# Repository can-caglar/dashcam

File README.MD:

# DASHCAM PROJECT

This is the development repo for a low-cost, dash-cam hobby project.

**Features:**

1. Small size (34 x 34 x 34 cm)

2. Saves videos to AVI format (motion JPEG).

3. Powered through a USB mini cable.

4. Can connect to WiFi. The idea is to connect it to your phone hotspot, after which the video will be streamed to a local server that the driver can access on their phone's internet browser. This is to help the driver position the camera by seeing what the camera is seing.

5. Small OLED screen and 3 buttons for the UI. OLED will show the device IP address for the video streaming server, and show nearby WiFi access points.

6. Inexpensive looking (due to very small design). Will not encourage thieves!

7. Has a supercapacitor which keeps power active for ~ 1 second after power is cut, this means videos will never be corrupt.

8. SD card slot which overrides oldest videos, so the device will never run out of memory. 

9. It's a cube! The x, y and z dimentions have been distributed equally so it takes up as little space from the driver's perspective as possible.

## Latest update:

**Proven concepts**

- Videos can be saved on an ESP32 using an AVI format.

- Supercapacitor keeps the device on long enough for the video to save after abrupt power down.

- OLED library allows scrolling text, so long messages, i.e. IP address of device can be shown easily. 

**Hardware**

PCB spin 1 has arrived and components have been soldered.

The ESP32 can be programmed and can run a basic "hello world" script without issues.

Full circuit could not be tested because the 0.5 mm pitch FPC connectors proved difficult to solder without a hot air gun.

More details can be found in [Project_planning.xlsx](https://github.com/jhancharler/dashcam/blob/master/project_plan/Project_planning.xlsx "Project_planning.xlsx").

## Images:

**Top-side images:**

**Back images:**

**Upright images:**

**In-car concept:**

**PCB view** 
*KiCAD files for the project can be found [here](https://github.com/jhancharler/dashcam/tree/master/hardware/schem_1)):
*

## Progress log

To see the progress log and design decisions, go to the /project_plan folder to see the various plan documents.

## Installation

Will be added once firmware is written for device.

```bash
```

## Usage

Will be added once firmware is written for device.

```python
```

## License
[MIT](https://choosealicense.com/licenses/mit/)

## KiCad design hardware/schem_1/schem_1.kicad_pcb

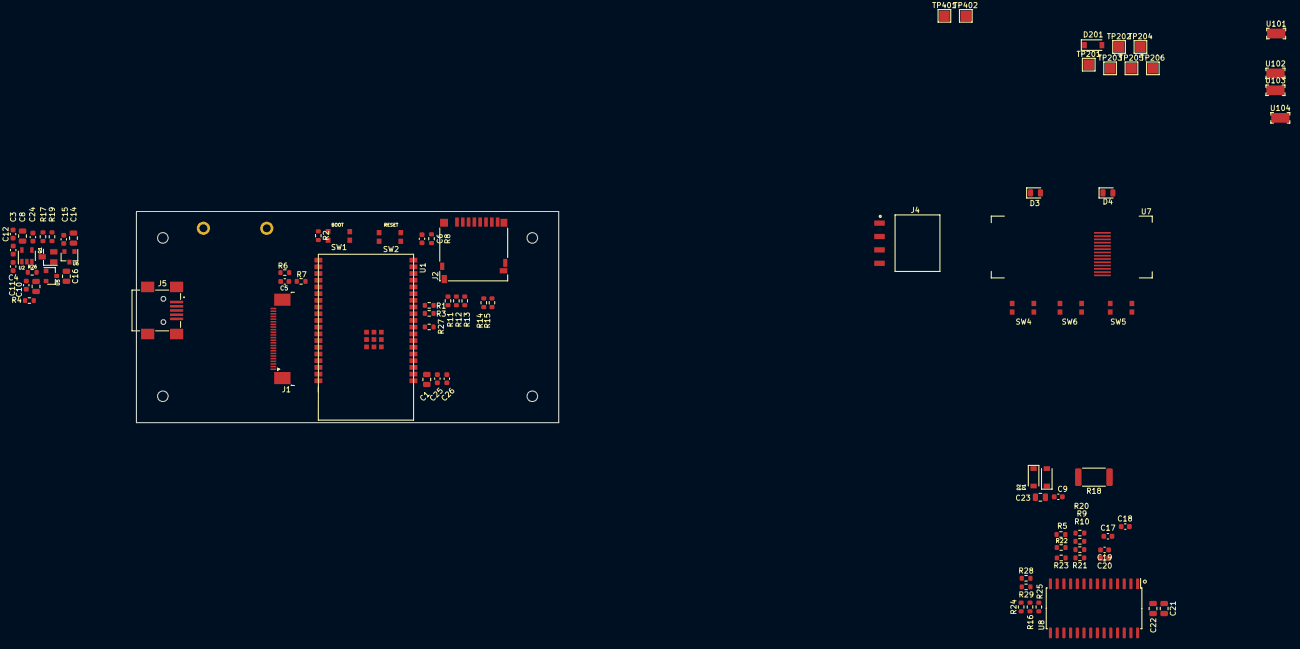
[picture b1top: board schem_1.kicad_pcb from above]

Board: 4 copper layers, 80.0 x 40.0 mm, 90 parts (1 on the bottom side), 56 nets, no tracks yet.

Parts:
C1: 47uF/6.3V/20%/0805; C_0805_2012Metric
C2: DGH105Q5R5; DGH105Q5R5-Horizontal
C3: 15pF; C_0603_1608Metric
C4, C5, C11, C15, C26: 0.1uF; C_0603_1608Metric
C6, C9, C12, C17, C18, C19, C20, C24, C25: 1uF; C_0603_1608Metric
C8: 10uF DNF; C_0805_2012Metric
C10, C14, C16, C21, C22, C23: 10uF; C_0805_2012Metric
D1, D2, D201: PMEG2005EGWX; D_SOD-123
D3: LED_GREEN; LED_0805_2012Metric
D4: LED; LED_0805_2012Metric
H1, H2, H3, H4: MountingHole; MountingHole_2mm
J1: OV7670_Conn_01x24_MountingPin; TE_2-1734839-4_1x24-1MP_P0.5mm_Horizontal
J2: Micro_SD_Card; microSD_HC_Hirose_DM3D-SF
J4: BG300-04-X-X-A_REVC; GCT_BG300-04-X-X-A_REVC
J5: UJ2-MBH-1-SMT; CUI_UJ2-MBH-1-SMT
Q1: NDS332P; SuperSOT-3
R1, R3, R6: 4.7K; R_0603_1608Metric
R2, R17, R20: 10k; R_0603_1608Metric
R4, R5: 0R; R_0603_1608Metric
R7: 1K; R_0603_1608Metric
R8: 10K; R_0603_1608Metric
R9, R10, R26, R27, R28, R29: 3.3k; R_0603_1608Metric
R11: DNC; R_0603_1608Metric
R12, R13, R14, R15: 47K; R_0603_1608Metric
R16, R25: 470; R_0603_1608Metric
R18: CRCW251224R0JNEG; R_2512_6332Metric
R19: 1k; R_0603_1608Metric
R21: 300k; R_0603_1608Metric
R22: 100k; R_0603_1608Metric
R23: 150k; R_0603_1608Metric
R24: 2k2; R_0603_1608Metric
SW1: BTN_BOOT; JC_Switch_TL6330
SW2: ESP32_RESET; JC_Switch_TL6330
SW4: DOWN; JC_Switch_TL6330
SW5: UP; JC_Switch_TL6330
SW6: OK; JC_Switch_TL6330
TP201, TP202, TP203, TP204, TP205, TP206, TP401, TP402: TestPoint; TestPoint_Pad_2.0x2.0mm
U1: ESP32-WROVER-E-JC
U2: XC6210B332MR; SOT-23-5
U5: XC6206-2.8V; SOT-23
U6: XC6206-1.2V; SOT-23
U7: 128x32_OLED_SSD1306; ER-OLED0.91-7W_SSD1306
U8: MCP23017_SO; SOIC-28W_7.5x17.9mm_P1.27mm
U101, U102, U103, U104: 0805_TEST_POINT; PC_TEST_POINT_SMD

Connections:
+1V2: C14.1, C15.1, J1.15, TP206.1, U6.2
+2V8: C10.1, C11.1, J1.21, TP205.1, U5.2
+3V3: C1.1, C4.2, C8.1, C19.1, C20.1, C24.1, C25.1, C26.1, J1.14, J2.4, Q1.3, R1.2, R2.1, R3.2, R6.2, R8.1, R9.1, R10.1, R11.1, R12.1, R13.1, R14.1, R15.1, R16.1, R17.1, R20.1, R24.1, R26.2, R27.1, R28.1, R29.1, TP203.1, U1.2, U2.5, U7.5, U7.8, U8.9
/5V_USB_SC: C9.1, C23.1, D2.2, D201.2, J4.4, J5.1, R22.1, TP201.1
/CAM_PWR: R19.2, TP204.1, U1.8
/CAM_RST: C5.1, J1.19, R6.1
/CSI_D0: R4.2, U1.29
/CSI_D1: J1.4, U1.30
/CSI_D2: J1.3, U1.31
/CSI_D3: J1.5, U1.33
/CSI_D4: J1.7, U1.4
/CSI_D5: J1.9, U1.5
/CSI_D6: J1.11, U1.6
/CSI_D7: J1.13, U1.7
/CSI_HSYNC: J1.16, U1.37
/CSI_MCLK: J1.12, R2.2, SW1.1, U1.25
/CSI_PCLK: C3.2, J1.8, U1.36
/CSI_VSYNC: J1.18, U1.10
/ESP32_RST: C6.1, R8.2, SW2.1, U1.3
/GPIO Expander/BTN_DOWN: SW4.1, U8.26
/GPIO Expander/BTN_OK: SW6.1, U8.28
/GPIO Expander/BTN_UP: SW5.1, U8.27
/GPIO Expander/LED_RECORDING: R25.1, U8.24
/GPIO Expander/Vusb_detect: R22.2, R23.1, TP401.1, U8.25
/HS2_CLK: J2.5, U1.13
/HS2_CMD: J2.3, R13.2, U1.23
/HS2_DATA0: J2.7, R14.2, U1.24
/HS2_DATA1: J2.8, R15.2, U1.26
/HS2_DATA2: J2.1, R11.2, U1.14
/HS2_DATA3: J2.2, R12.2, U1.16
/I2C OLED/OLED_RESET: R20.2, U7.9
/SCL: J4.2, R9.2, R26.1, R29.2, U1.34, U7.10, U8.12, U103.1
/SDA: R10.2, R27.2, R28.2, U1.9, U7.11, U8.13, U101.1
/TWI_SCK: J1.20, R1.1, U1.12
/TWI_SDA: J1.22, R3.1, U1.11
/U0TXD: J4.3, U1.35, U102.1
GND: C1.2, C3.1, C4.1, C5.2, C6.2, C8.2, C9.2, C10.2, C11.2, C12.2, C14.2, C15.2, C16.2, C19.2, C20.2, C21.2, C22.2, C23.2, C24.2, C25.2, C26.2, D3.1, D4.1, J1.10, J1.23, J1.MP, J2.6, J2.9, J4.1, J5.5, J5.SH1, J5.SH2, J5.SH3, J5.SH4, R7.1, R21.2, R23.2, SW1.2, SW2.2, SW4.2, SW5.2, SW6.2, U1.1, U1.15, U1.38, U1.39, U2.2, U5.1, U6.1, U7.7, U8.10, U8.15, U8.16, U8.17, U104.1
unnamed: C12.1, D1.1, D201.1, TP202.1, U2.1, U2.3
unnamed: C16.1, Q1.1, U5.3, U6.3
unnamed: C17.1, U7.1
unnamed: C17.2, U7.2
unnamed: C18.1, U7.3
unnamed: C18.2, U7.4
unnamed: C21.1, U7.13
unnamed: C22.1, U7.14
unnamed: D1.2, R18.2
unnamed: D2.1, R18.1
unnamed: D3.2, R16.2
unnamed: D4.2, R25.2
unnamed: J1.6, R4.1
unnamed: J1.17, R7.2
unnamed: J5.2, R5.1
unnamed: J5.3, R5.2
unnamed: Q1.2, R17.2, R19.1
unnamed: R21.1, U7.12
unnamed: R24.2, TP402.1, U8.18

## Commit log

2021-04-24 add project plan template
2021-04-24 finish project planning, add block diagram, add readme, gitignore
2021-04-24 update folders
2021-04-24 set up esp idf, vscode, and the start program.
2021-04-24 add submodule
2021-05-08 start schematic design. add use scenario. update notes.
2021-05-16 update gitignore to ignore kicad files
2021-05-16 add 128x32 oled to schem. add new symbols to library. add backup power (supercap) circuit. update plan. add esp32 pinouts
2021-05-22 update schematic: add io expander with peripherals, update power circuitry- change some components. update project plan. update footprints
2021-05-23 Replace ESP32 Wroom module with WRover and remove the external PSRAM (as Wrover has one built in). Create symbol and footprint for Wrover. Update footprints for resistors and buttons. Update USB foot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
2021-05-29 change supercap for one with lower esr and shorter. create footprint and 3d model for new cap. remove power switch entirely.
2021-05-30 update footprint for OLED display (no longer using ffc connector)
2021-06-05 update footprints for 24way connector, 3D models. add new connector to connect the two PCB's
2021-06-12 add correct 3d model for esp32 wrover e. initial placement of components done for both boards. need to start routing
2021-06-13 lay tracks and zones for front pcb.
2021-06-19 finish first round tracks and filled zones for front PCB. Do silk screen
2021-06-20 finish laying tracks and the layers on back pcb. modify some footprints as their courtyards were giving errors. 0 drc errors
2021-06-20 joined the PCBs together with mouse bites
2021-06-20 'productionize' the hardware. update project plan spreadsheet'
2021-08-01 update to latest gerbers, update project plan
2021-08-01 update README, add image folder
2021-08-22 add new update to project log. all 3 24-way fpc's connected. will continue validating hardware and make relevant changes for spin 2
2021-08-29 move old production stuff to new folder. start pcb spin 2: add test points (smd and pads). add third diode as currently disconnected USB can not be detected. increase LED resistor values are too brig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
2021-08-30 make board on breadboard for easier debugging and fixing. will start writing f/w on this board
2021-09-05 start fw- this commit is just file structure
2021-09-05 submodule added with esp idf lib that contains extra components. we will use the i/o expander mcp
2021-09-11 start writing mcp2017 driver. testing register writes/reads in this push
2021-09-11 test led blinking through io expander (works)
2021-09-11 create a quick API. Write a test routine in main to excersize all inputs and outputs.
2021-09-12 add interrupt init functions
